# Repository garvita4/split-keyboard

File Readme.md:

# A Split Keyboard, Built from Scratch

## Overview

This is a custom split mechanical keyboard that I designed with two ESP32-S3 microcontrollers, one for each half. I added a few extra features different from a normal keyboard, including 1.8-inch TFT displays, rotary encoders, RFID/NFC-based locking, and adjustable per-key backlighting.
This keyboard can be used as wired keybaord as well as the wireless keybaord with the 2 bluetooth profile 

##  Collaboration & Attribution (Team Project)

This project was built in collaboration with my friend **Mr. Chronos** ([Chronos-03/Chronos-keybaord](https://github.com/Chronos-03/Chronos-keybaord)).as I was learning several things from scratch, we worked together over meet sessions. our files look very similar beause they were made side by side in real time. I created my own project files step-by-step alongside him and mutually debugged issues.
you'll see that my schematics and pcb are exactly same as Mr. Chronos, so i wanna clarify that my schematic was made by me only and it looks same bcz we did it side by side together on our own projects, and about the pcb, it is Mr. Chronos's pcb.

###  Breakdown of Contributions (What I Did vs. What Chronos Did)

**What I Did Myself (Time Claimed):**
Drew the complete schematic in KiCad myself while following along in real time, verifying component connections, and helping spot/fix schematic errors during our sessions.Placed the components, routed the PCB tracks on my board, and resolved the DRC/ERC errors with his help. Built the 3D case step-by-step while learning CAD modeling from him. I also independently modified and fine-tuned my case design by adding rounded corners (fillets) to give it a smoother, distinct aesthetic compared to his.

**What Mr. Chronos Did (Time NOT Claimed):**
Guided me through the schematic design, PCB routing rules, error resolution, and 3D CAD workflow via screen share.The PCB panelization / mouse bites and shared fabrication prep were done directly by Mr. Chronos. **I have not claimed any time for this part.**

## Why did i make this
I just wanted to make something cool which i myself yould love to use in a long run.And this idea came randomly, while discussing projects with my friend Mr. Chronos.We both liked the idea, so we decided to stick with it and gradually started adding more features to make it our own.

## Key Features

### Split Mechanical Layout

the keyboard is in two separate halves, with each half having its own ESP32-S3 microcontroller. Each side has 21 Cherry MX switches, giving the keyboard a total of 42 keys. I also included individual backlighting for the keys.

### Rotary Encoder Controls

EC11 rotary encoders helps in  easily adjusting settings like volume and screen brightness.

### TFT Display

Two 1.8-inch TFT displays show information like battery level and connection status. They can also play animations when the keyboard is not in use.

### RFID Integration

integrated an RC522 RFID reader into each half. This allows the keyboard to read RFID cards and NFC tags. I also added the option to use this feature as a keyboard lock or to trigger PC unlocking through a supported NFC tag or phone.

### Rechargeable Power

Each half has a rechargeable 10,000 mAh LiPo battery and a built-in BMS to power all its components. this can provide long battery life when using Bluetooth mode.

### Per-Key Backlighting

White 0603 SMD LEDs are use to work as the backlight like any professional keybaord. its intensity can be controlled  with the same rotatory encoder.

## Schematic Design

### Key Switch Matrix

The switch matrix connects the mechanical switches to the microcontroller. diodes prevent unwanted signals when multiple keys are pressed at the same time.

### Switches and Diodes

Each mechanical switch registers an individual key press, while the 1N4148WS diodes help prevent unwanted signal interference when multiple keys are pressed together.

### Resistors and LEDs

Resistors support the circuits and help in its proper working, while white SMD LEDs provide backlighting for each key.

### Microcontroller

The ESP32-S3-WROOM-1-N4R8 acts as the main controller for each half.

### Rotary Encoders

The EC11 encoders can be pressed or rotated to access additional keyboard controls.

### Display Circuit

The TFT displays are connected to the ESP32-S3 so they can show battery information, connection status, and other keyboard details.

### RFID Circuit

The RC522 modules are connected to the ESP32-S3 to read RFID cards and NFC tags.

### Power Management

For the power section, TP4056 charging ICs, ME6211 voltage regulators and AO3400A MOSFETs are used. I also added resettable PTC protection.

### USB-C Connectivity

The USB-C ports are used for charging, uploading firmware, and connecting the keyboard using a wired connection.

## PCB Design

The schematic and PCB layout were designed in KiCad, and the boards are manufactured by Zbotic. The PCB contains the keyboard matrix, controller connections, peripheral interfaces, LED backlighting, and power circuits.

## CAD Design

The keyboard case was designed in Fusion 360 to fit all the components, including the custom PCB, switches, displays, rotary encoders, and other internal electronics.

### Enclosure

### Complete Assembly

## Firmware Status

I wrote the firmware before the physical hardware was assembled, so I haven't been able to test it on the actual PCB yet. Once the boards are ready, I'll flash them and check each component individually. I'll make changes wherever needed and update the code based on how everything performs on the actual hardware.

**AI Disclosure:** AI tools were used for firmware development. I initially considered existing keyboard firmware frameworks like QMK and ZMK, but their hardware support and existing implementations didn't directly fit all the requirements of this project. QMK has limited built-in Bluetooth support, while ZMK's tested hardware support does not directly cover my ESP32-S3 setup, and its display support is still under development. Integrating all the additional features, including the TFT displays, rotary encoders, RFID/NFC modules, and individually controlled backlighting, would therefore require additional customization.

The firmware was built using the Arduino framework with full help of AI...so the firmware is heavily vibecoded .....i'll make one when the hardware part is done.**AI assistance was limited to the firmware side of the project.** The hardware design, schematic capture, and 3D CAD modeling were done separately by me, alongside guidance and pcb from Mr. Chronos.

## Display, Backlight, and NFC Features

Some additional features that I added to this project:
* **Display:** A 1.8-inch SPI TFT display that shows battery status, backlight brightness, the active layer, and NFC tag UIDs.
* **Backlight:** 0603 SMD LEDs with PWM brightness control through the rotary encoder and wireless syncing.
* **NFC:** An RC522 NFC module connected through SPI for scanning NFC tags.

Getting the display, backlight, and NFC features working alongside the wireless keyboard took quite a bit of work. I had to make changes to the firmware to get everything working together. The firmware is ready for testing, but the actual on-board checks and final testing will be done once the physical hardware is assembled.

## Bill of Materials (BOM)

| Item | Qty | Supplier | Cost/item | Total Cost | Link |
| :--- | :--- | :--- | :--- | :--- | :--- |
| ESP32-S3-WROOM-1 Module | 2 | Robu.in | $6.03 | $12.06 | [Buy](https://robu.in/product/espressif-esp32-s3-wroom-1-n16r8-module/) |
| NFC RFID Reader | 2 | IndianHobbyCenter | $1.47 | $2.94 | [Buy](https://www.indianhobbycenter.com/products/rc522-mini-rfid-reader-writer-spi-s50-with-rfid-card-and-tag) |
| PCB | 1 | Zbotic | $45.00 | $45.00 | [Buy](https://zbotic.in/) |
| 1.8" TFT Display | 2 | Robu.in | $3.28 | $6.56 | [Buy](https://robu.in/product/62060/) |
| Cherry MX2A Mechanical Switches | 42 | meckeys | $0.41 | $17.22 | [Buy](https://meckeys.com/shop/accessories/keyboard-accessories/key-switches/cherry-mx2a-switch/) |
| 1N4148WS SMD Diodes (SOD-323) | 42 | surnom.com | $0.01 | $0.42 | [Buy](https://www.sunrom.com/p/1n4148---1n4148ws---t4---smd---sod323-0805) |
| EC11 Rotary Encoder | 2 | robu.in | $0.61 | $1.22 | [Buy](https://robu.in/product/hongyan-ec11h-7ce15p1zd15f7-rotary-encoder-with-push-button-switch-vertical-plug-in-5-pin-360-degree/) |
| 0603 SMD Backlight LEDs | 42 | ktron.in | $0.01 | $0.42 | [Buy](https://www.ktron.in/product/smd-white-led-0603-package/) |
| AO3400A N-Channel MOSFET | 2 | robu.in | $0.06 | $0.12 | [Buy](https://robu.in/product/1-month-warranty-414/) |
| SMD 16-pin connector | 4 | ktron.in | $0.06 | $0.24 | [Buy](https://www.ktron.in/product/16-pin-usb-type-c-connector-smd/) |
| 10,000 mAh LiPo Battery | 2 | makerbazar.in | $4.23 | $8.46 | [Buy](https://makerbazar.in/products/single-cell-3-7v-10000mah-lipo-battery) |
| TP4056 IC | 2 | ktron.in | $0.05 | $0.10 | [Buy](https://www.ktron.in/product/tp4056-ic/) |
| ME6211A33M3G IC | 2 | Robu.in | $0.08 | $0.16 | [Buy](https://robu.in/product/me6211c33m5g-n-microne-500ma-fixed-3-3v-positive-electrode-6v-sot-23-5-voltage-regulators-linear-low-drop-out-ldo-regulators-rohs/) |
| SMD1206P050TF/13.2 (PTC) | 2 | Robu.in | $0.10 | $0.20 | [Buy](https://robu.in/product/smd1206-050c-6v-bnstar-6v-40a-500ma-1a-1206-resettable-rohs/) |
| SMD Push Switches | 4 | Robu.in | $0.05 | $0.20 | [Buy](https://robu.in/product/tsa043a2026a-bzcn-3x4x2-5-50ma-round-button-50gf-12v-smd-tactile-switches-rohs/) |
| Slide Switch | 2 | Robu.in | $0.03 | $0.06 | [Buy](https://robu.in/product/1-month-warranty-254/) |
| 100Ω Resistor | 42 | ktron.in | $0.01 | $0.42 | [Buy](https://www.ktron.in/product/resistor-100-ohms-1-1-8w-smd-0805/) |
| 10kΩ Resistor | 12 | ktron.in | $0.01 | $0.12 | [Buy](https://www.ktron.in/product/resistor-10k-ohms-1-1-8w-smd-0805/) |
| 56kΩ Resistor | 4 | ktron.in | $0.01 | $0.04 | [Buy](https://www.ktron.in/product/resistor-56k-ohms-1-1-8w-smd-0805/) |
| 5.1kΩ Resistor | 4 | ktron.in | $0.01 | $0.04 | [Buy](https://www.ktron.in/product/resistor-5k1-ohms-5-1-8w-smd-0805/) |
| 1.2kΩ Resistor | 2 | ktron.in | $0.01 | $0.02 | [Buy](https://www.ktron.in/product/resistor-1k2-ohms-1-1-8w-smd-0805/) |
| 10µF Capacitor | 10 | ktron.in | $0.08 | $0.80 | [Buy](https://www.ktron.in/product/10uf-50v-multi-layered-ceramic-capacitor-mlcc-x5r-smd-0805-yageo-cc0805kkx5r9bb106/) |
| 1µF Capacitor | 2 | ktron.in | $0.09 | $0.18 | [Buy](https://www.ktron.in/product/1uf-50v-multi-layered-ceramic-capacitor-yageo/) |
| 100nF Capacitor | 8 | ktron.in | $0.01 | $0.08 | [Buy](https://www.ktron.in/product/100nf-25v-multi-layered-ceramic-capacitor/) |
| Estimated total shipping | 1 | | | $0.00 | |
| **Grand Total** | | | | **$97.08** | |

## Tools & Technologies

- **PCB Design:** KiCad
- **CAD Modelling:** Fusion 360
- **Firmware:** Cpp, Arduino, FreeRTOS
- **Microcontroller:** ESP32-S3
- **PCB Manufacturing:** Zbotic

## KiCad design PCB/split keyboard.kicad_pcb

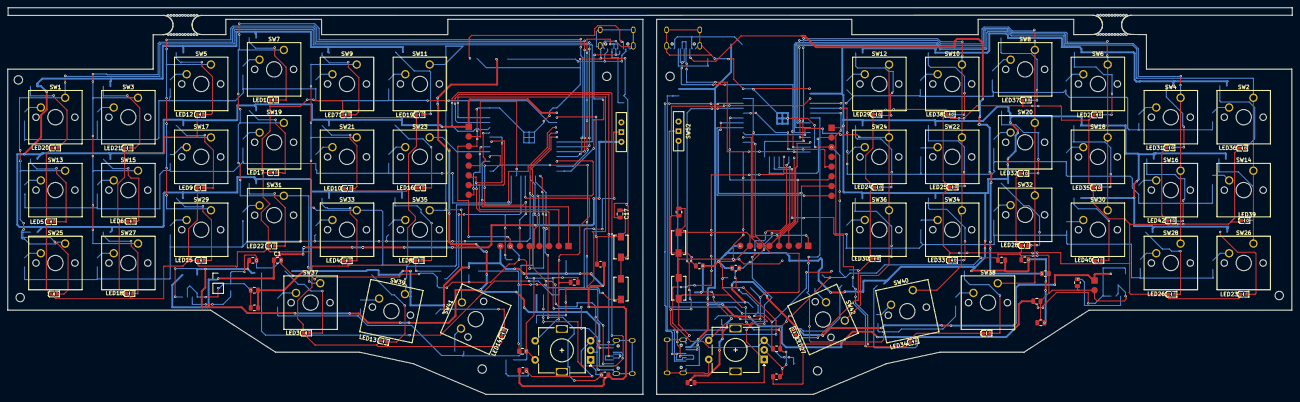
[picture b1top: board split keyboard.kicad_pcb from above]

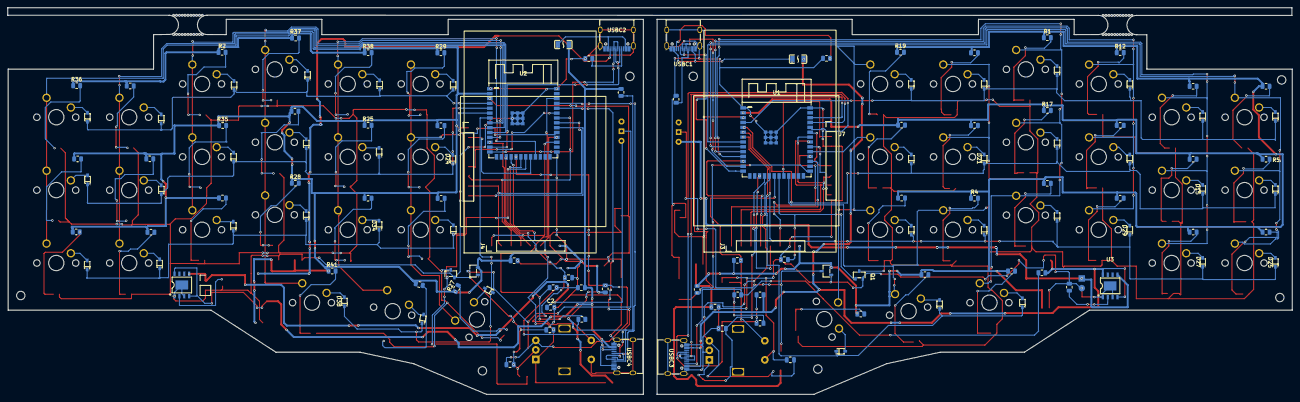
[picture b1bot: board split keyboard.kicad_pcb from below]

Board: 2 copper layers, 335.7 x 101.0 mm, 244 parts (127 on the bottom side), 166 nets.

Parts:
C1, C2, C5, C6, C11, C12, C13, C14: 10u; C_0805_2012Metric
C3, C4: 10U; C_0805_2012Metric
C7, C8, C9, C10, C15, C16, C19, C20: 100n; C_0805_2012Metric
C17, C18: 1u; C_0805_2012Metric
D1, D2, D3, D4, D5, D6, D7, D8, D9, D10, D11, D12, D13, D14, D15, D16, D17, D18, D19, D20, D21, D22, D23, D24, D25, D26, D27, D28, D29, D30, D31, D32, D33, D34, D35, D36, D37, D38, D39, D40, D41, D42: 1N4148WS T4; SOD-323_L1.8-W1.3-LS2.5-RD
F1, F2: SMD1206P050TF/13.2_C393935; F1206
J3, J4: TFTTT; PinHeader_1x08_P2.54mm_Vertical
J5, J6: BATT; PinHeader_1x02_P2.54mm_Vertical
J7, J8: NFC2; PinHeader_1x08_P2.54mm_Vertical
LED1, LED2, LED3, LED4, LED5, LED6, LED7, LED8, LED9, LED10, LED11, LED12, LED13, LED14, LED15, LED16, LED17, LED18, LED19, LED20, LED21, LED22, LED23, LED24, LED25, LED26, LED27, LED28, LED29, LED30, LED31, LED32, LED33, LED34, LED35, LED36, LED37, LED38, LED39, LED40, LED41, LED42: BL; LED0603-R-RD_WHITE
Q1, Q2: AO3400A; SOT-23-3_L2.9-W1.3-P1.90-LS2.4-BR
R1, R2, R3, R4, R5, R6, R7, R8, R9, R10, R11, R12, R13, R14, R15, R16, R17, R18, R19, R20, R21, R22, R23, R24, R25, R26, R27, R28, R29, R30, R31, R32, R33, R34, R35, R36, R37, R38, R39, R40, R41, R42: 0805; R_0805_2012Metric
R43, R44, R47, R48, R55, R56, R57, R58, R59, R60, R65, R66: 10k; R_0805_2012Metric
R45, R46, R51, R52, R61, R62, R63, R64: 5.1k; R_0805_2012Metric
R49, R50: 1.2K; R_0805_2012Metric
R67, R68, R69, R70: 56k; R_0805_2012Metric
SW1, SW2, SW3, SW4, SW5, SW6, SW7, SW8, SW9, SW10, SW11, SW12, SW13, SW14, SW15, SW16, SW17, SW18, SW19, SW20, SW21, SW22, SW23, SW24, SW25, SW26, SW27, SW28, SW29, SW30, SW31, SW32, SW33, SW34, SW35, SW36, SW37, SW38, SW39, SW40: SW_Push; SW_Cherry_MX_1.00u_PCB
SW41, SW42: SW_Push; SW_Cherry_MX_1.50u_PCB
SW43, SW44: RotaryEncoder_Switch; RotaryEncoder_Alps_EC11E-Switch_Vertical_H20mm
SW47, SW49: reset; SW_SPST_EVQPE1
SW48, SW50: boot; SW_SPST_EVQPE1
SW51, SW52: SW_Wuerth_450301014042; SW_Slide-03_Wuerth-WS-SLTV_10x2.5x6.4_P2.54mm
U1, U2: ESP32-S3-WROOM-1-N4R8; WIRELM-SMD_ESP32-S3-WROOM-1
U3, U4: TP4056_C725790; ESOP-8_L4.9-W3.9-P1.27-LS6.0-BL-EP
U5, U6: ME6211A33M3G-N; SOT-23-3_L2.9-W1.6-P1.90-LS2.8-BR
USBC1, USBC2: TYPE-C-31-M-12; USB-C_SMD-TYPE-C-31-M-12_1
USBC3, USBC4: J_LINK; USB-C_SMD-TYPE-C-31-M-12_1
mouse-bite-5mm-slot, mouse-bite-5mm-slot#2: VAL**; mouse-bite-5mm-slot

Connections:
+3.3V: C11.2, C12.2, C13.2, C14.2, C15.2, C16.2, J3.8, J4.8, J7.1, J8.1, R1.1, R2.1, R3.1, R4.1, R5.1, R6.1, R7.1, R8.1, R9.1, R10.1, R11.1, R12.1, R13.1, R14.1, R15.1, R16.1, R17.1, R18.1, R19.1, R20.1, R21.1, R22.1, R23.1, R24.1, R25.1, R26.1, R27.1, R28.1, R29.1, R30.1, R31.1, R32.1, R33.1, R34.1, R35.1, R36.1, R37.1, R38.1, R39.1, R40.1, R41.1, R42.1, R47.1, R48.1, R55.1, R56.1, R57.1, R58.1, R59.2, R60.2, R65.2, R66.2, U1.2 (3V3), U2.2 (3V3), U5.2 (VOUT), U6.2 (VOUT)
/left/5V_USB: C3.1, F1.2, R61.2, R63.2, U3.4 (VCC), U3.8 (CE), USBC3.A4B9 (VBUS), USBC3.B4A9 (VBUS)
/left/BACKLIGHT_PWM: Q1.1 (G), R43.1, U1.21 (IO13)
/left/COL0: SW1.1, SW13.1, SW25.1, U1.8 (IO15)
/left/COL1: SW3.1, SW15.1, SW27.1, U1.9 (IO16)
/left/COL2: SW5.1, SW17.1, SW29.1, U1.10 (IO17)
/left/COL3: SW7.1, SW19.1, SW31.1, SW37.1, U1.11 (IO18)
/left/COL4: SW9.1, SW21.1, SW33.1, SW39.1, U1.23 (IO21)
/left/COL5: SW11.1, SW23.1, SW35.1, SW41.1, U1.31 (IO38)
/left/ENCODER_A: C7.1, R55.2, SW43.A, U1.18 (IO10)
/left/ENCODER_B: C9.1, R57.2, SW43.B, U1.19 (IO11)
/left/ENCODER_SW: C19.1, R47.2, SW43.S1, U1.20 (IO12)
/left/HOST_PWR_EN: R67.1, R68.1, U1.38 (IO2)
/left/INTER_RX: U1.36 (RXD0), USBC3.A7 (DN1), USBC3.B7 (DN2)
/left/INTER_TX: U1.37 (TXD0), USBC3.A6 (DP1), USBC3.B6 (DP2)
/left/LED_CATHODE: LED1.2 (K), LED3.2 (K), LED4.2 (K), LED5.2 (K), LED6.2 (K), LED7.2 (K), LED8.2 (K), LED9.2 (K), LED10.2 (K), LED11.2 (K), LED12.2 (K), LED13.2 (K), LED14.2 (K), LED15.2 (K), LED16.2 (K), LED17.2 (K), LED18.2 (K), LED19.2 (K), LED20.2 (K), LED21.2 (K), LED22.2 (K), Q1.3 (D)
/left/ROW0: D1.1 (K), D3.1 (K), D5.1 (K), D7.1 (K), D9.1 (K), D11.1 (K), U1.4 (IO4)
/left/ROW1: D13.1 (K), D15.1 (K), D17.1 (K), D19.1 (K), D21.1 (K), D23.1 (K), U1.5 (IO5)
/left/ROW2: D25.1 (K), D27.1 (K), D29.1 (K), D31.1 (K), D33.1 (K), D35.1 (K), U1.6 (IO6)
/left/ROW3: D37.1 (K), D39.1 (K), D41.1 (K), U1.7 (IO7)
/left/SPI_CS: J7.8, U1.32 (IO39)
/left/SPI_MISO: J7.5, U1.35 (IO42)
/left/SPI_MOSI: J3.3, J7.6, U1.34 (IO41)
/left/SPI_RST: J7.2, U1.22 (IO14)
/left/SPI_SCK: J3.2, J7.7, U1.33 (IO40)
/left/TFT_CS: J3.6, U1.30 (IO37)
/left/TFT_DC: J3.4, U1.12 (IO8)
/left/TFT_PWM: J3.1, U1.29 (IO36)
/left/TFT_RST: J3.5, U1.17 (IO9)
/left/USB_D+: U1.14 (IO20), USBC1.A6 (DP1), USBC1.B6 (DP2)
/left/USB_D-: U1.13 (IO19), USBC1.A7 (DN1), USBC1.B7 (DN2)
/left/VBAT: C1.1, J5.1, SW51.3 (A), U3.5 (BAT)
/right/5V_USB: C4.1, F2.2, R62.2, R64.2, U4.4 (VCC), U4.8 (CE), USBC4.A4B9 (VBUS), USBC4.B4A9 (VBUS)
/right/BACKLIGHT_PWM: Q2.1 (G), R44.1, U2.21 (IO13)
/right/COL0: SW2.1, SW14.1, SW26.1, U2.8 (IO15)
/right/COL1: SW4.1, SW16.1, SW28.1, U2.9 (IO16)
/right/COL2: SW6.1, SW18.1, SW30.1, U2.10 (IO17)
/right/COL3: SW8.1, SW20.1, SW32.1, SW38.1, U2.11 (IO18)
/right/COL4: SW10.1, SW22.1, SW34.1, SW40.1, U2.23 (IO21)
/right/COL5: SW12.1, SW24.1, SW36.1, SW42.1, U2.31 (IO38)
/right/ENCODER_A: C8.1, R56.2, SW44.A, U2.18 (IO10)
/right/ENCODER_B: C10.1, R58.2, SW44.B, U2.19 (IO11)
/right/ENCODER_SW: C20.1, R48.2, SW44.S1, U2.20 (IO12)
/right/HOST_PWR_EN: R69.1, R70.1, U2.38 (IO2)
/right/INTER_RX: U2.36 (RXD0), USBC4.A7 (DN1), USBC4.B7 (DN2)
/right/INTER_TX: U2.37 (TXD0), USBC4.A6 (DP1), USBC4.B6 (DP2)
/right/LED_CATHODE: LED2.2 (K), LED23.2 (K), LED24.2 (K), LED25.2 (K), LED26.2 (K), LED27.2 (K), LED28.2 (K), LED29.2 (K), LED30.2 (K), LED31.2 (K), LED32.2 (K), LED33.2 (K), LED34.2 (K), LED35.2 (K), LED36.2 (K), LED37.2 (K), LED38.2 (K), LED39.2 (K), LED40.2 (K), LED41.2 (K), LED42.2 (K), Q2.3 (D)
/right/ROW0: D2.1 (K), D4.1 (K), D6.1 (K), D8.1 (K), D10.1 (K), D12.1 (K), U2.4 (IO4)
/right/ROW1: D14.1 (K), D16.1 (K), D18.1 (K), D20.1 (K), D22.1 (K), D24.1 (K), U2.5 (IO5)
/right/ROW2: D26.1 (K), D28.1 (K), D30.1 (K), D32.1 (K), D34.1 (K), D36.1 (K), U2.6 (IO6)
/right/ROW3: D38.1 (K), D40.1 (K), D42.1 (K), U2.7 (IO7)
/right/SPI_CS: J8.8, U2.32 (IO39)
/right/SPI_MISO: J8.5, U2.35 (IO42)
/right/SPI_MOSI: J4.3, J8.6, U2.34 (IO41)
/right/SPI_RST: J8.2, U2.22 (IO14)
/right/SPI_SCK: J4.2, J8.7, U2.33 (IO40)
/right/TFT_CS: J4.6, U2.30 (IO37)
/right/TFT_DC: J4.4, U2.12 (IO8)
/right/TFT_PWM: J4.1, U2.29 (IO36)
/right/TFT_RST: J4.5, U2.17 (IO9)
/right/USB_D+: U2.14 (IO20), USBC2.A6 (DP1), USBC2.B6 (DP2)
/right/USB_D-: U2.13 (IO19), USBC2.A7 (DN1), USBC2.B7 (DN2)
/right/VBAT: C2.1, J6.1, SW52.3 (A), U4.5 (BAT)
GND: C1.2, C2.2, C3.2, C4.2, C5.2, C6.2, C7.2, C8.2, C9.2, C10.2, C11.1, C12.1, C13.1, C14.1, C15.1, C16.1, C17.2, C18.2, C19.2, C20.2, J3.7, J4.7, J5.2, J6.2, J7.3, J8.3, Q1.2 (S), Q2.2 (S), R43.2, R44.2, R45.2, R46.2, R49.1, R50.1, R51.2, R52.2, SW43.C, SW43.S2, SW44.C, SW44.S2, SW47.1, SW48.2, SW49.1, SW50.2, U1.1 (GND), U1.40 (GND), U1.41 (GND), U2.1 (GND), U2.40 (GND), U2.41 (GND), U3.1 (TEMP), U3.3 (GND), U3.9 (EP), U4.1 (TEMP), U4.3 (GND), U4.9 (EP), U5.1 (VSS), U6.1 (VSS), USBC1.1 (EH), USBC1.2 (EH), USBC1.3 (EH), USBC1.4 (EH), USBC1.A1B12 (GND), USBC1.B1A12 (GND), USBC2.1 (EH), USBC2.2 (EH), USBC2.3 (EH), USBC2.4 (EH), USBC2.A1B12 (GND), USBC2.B1A12 (GND), USBC3.1 (EH), USBC3.2 (EH), USBC3.3 (EH), USBC3.4 (EH), USBC3.A1B12 (GND), USBC3.B1A12 (GND), USBC4.1 (EH), USBC4.2 (EH), USBC4.3 (EH), USBC4.4 (EH), USBC4.A1B12 (GND), USBC4.B1A12 (GND)
unnamed: D1.2 (A), SW1.2
unnamed: D2.2 (A), SW2.2
unnamed: D3.2 (A), SW3.2
unnamed: D4.2 (A), SW4.2
unnamed: D5.2 (A), SW5.2
unnamed: D6.2 (A), SW6.2
unnamed: D7.2 (A), SW7.2
unnamed: D8.2 (A), SW8.2
unnamed: D9.2 (A), SW9.2
unnamed: D10.2 (A), SW10.2
unnamed: D11.2 (A), SW11.2
unnamed: D12.2 (A), SW12.2
unnamed: D13.2 (A), SW13.2
unnamed: D14.2 (A), SW14.2
unnamed: D15.2 (A), SW15.2
unnamed: D16.2 (A), SW16.2
unnamed: D17.2 (A), SW17.2
unnamed: D18.2 (A), SW18.2
unnamed: D19.2 (A), SW19.2
unnamed: D20.2 (A), SW20.2
unnamed: D21.2 (A), SW21.2
unnamed: D22.2 (A), SW22.2
unnamed: D23.2 (A), SW23.2
unnamed: D24.2 (A), SW24.2
unnamed: D25.2 (A), SW25.2
unnamed: D26.2 (A), SW26.2
unnamed: D27.2 (A), SW27.2
unnamed: D28.2 (A), SW28.2
unnamed: D29.2 (A), SW29.2
unnamed: D30.2 (A), SW30.2
unnamed: D31.2 (A), SW31.2
unnamed: D32.2 (A), SW32.2
unnamed: D33.2 (A), SW33.2
unnamed: D34.2 (A), SW34.2
unnamed: D35.2 (A), SW35.2
unnamed: D36.2 (A), SW36.2
unnamed: D37.2 (A), SW37.2
unnamed: D38.2 (A), SW38.2
unnamed: D39.2 (A), SW39.2
unnamed: D40.2 (A), SW40.2
unnamed: D41.2 (A), SW41.2
unnamed: D42.2 (A), SW42.2
unnamed: F1.1, USBC1.A4B9 (VBUS), USBC1.B4A9 (VBUS)
unnamed: F2.1, USBC2.A4B9 (VBUS), USBC2.B4A9 (VBUS)
unnamed: LED1.1 (A), R1.2
unnamed: LED2.1 (A), R2.2
unnamed: LED3.1 (A), R3.2
unnamed: LED4.1 (A), R4.2
unnamed: LED5.1 (A), R5.2
unnamed: LED6.1 (A), R6.2
unnamed: LED7.1 (A), R7.2
unnamed: LED8.1 (A), R8.2
unnamed: LED9.1 (A), R9.2
unnamed: LED10.1 (A), R10.2
unnamed: LED11.1 (A), R11.2
unnamed: LED12.1 (A), R12.2
unnamed: LED13.1 (A), R13.2
unnamed: LED14.1 (A), R14.2
unnamed: LED15.1 (A), R15.2
unnamed: LED16.1 (A), R16.2
unnamed: LED17.1 (A), R17.2
unnamed: LED18.1 (A), R18.2
unnamed: LED19.1 (A), R19.2
unnamed: LED20.1 (A), R20.2
unnamed: LED21.1 (A), R21.2
unnamed: LED22.1 (A), R22.2
unnamed: LED23.1 (A), R23.2
unnamed: LED24.1 (A), R24.2
unnamed: LED25.1 (A), R25.2
unnamed: LED26.1 (A), R26.2
unnamed: LED27.1 (A), R27.2
unnamed: LED28.1 (A), R28.2
unnamed: LED29.1 (A), R29.2
unnamed: LED30.1 (A), R30.2
unnamed: LED31.1 (A), R31.2
unnamed: LED32.1 (A), R32.2
unnamed: LED33.1 (A), R33.2
unnamed: LED34.1 (A), R34.2
unnamed: LED35.1 (A), R35.2
unnamed: LED36.1 (A), R36.2
unnamed: LED37.1 (A), R37.2
unnamed: LED38.1 (A), R38.2
unnamed: LED39.1 (A), R39.2
unnamed: LED40.1 (A), R40.2
unnamed: LED41.1 (A), R41.2
unnamed: LED42.1 (A), R42.2
unnamed: C5.1, SW51.1 (B), U5.3 (VIN)
unnamed: C6.1, SW52.1 (B), U6.3 (VIN)
unnamed: C17.1, R65.1, SW47.2, U1.3 (EN)
unnamed: R59.1, SW48.1, U1.27 (IO0)
unnamed: C18.1, R66.1, SW49.2, U2.3 (EN)
unnamed: R60.1, SW50.1, U2.27 (IO0)
unnamed: R49.2, U3.2 (PROG)
unnamed: R50.2, U4.2 (PROG)
unnamed: R45.1, USBC1.A5 (CC1)
unnamed: R51.1, USBC1.B5 (CC2)
unnamed: R46.1, USBC2.A5 (CC1)
unnamed: R52.1, USBC2.B5 (CC2)
unnamed: R61.1, R68.2, USBC3.A5 (CC1)
unnamed: R63.1, R67.2, USBC3.B5 (CC2)
unnamed: R62.1, R70.2, USBC4.A5 (CC1)
unnamed: R64.1, R69.2, USBC4.B5 (CC2)
